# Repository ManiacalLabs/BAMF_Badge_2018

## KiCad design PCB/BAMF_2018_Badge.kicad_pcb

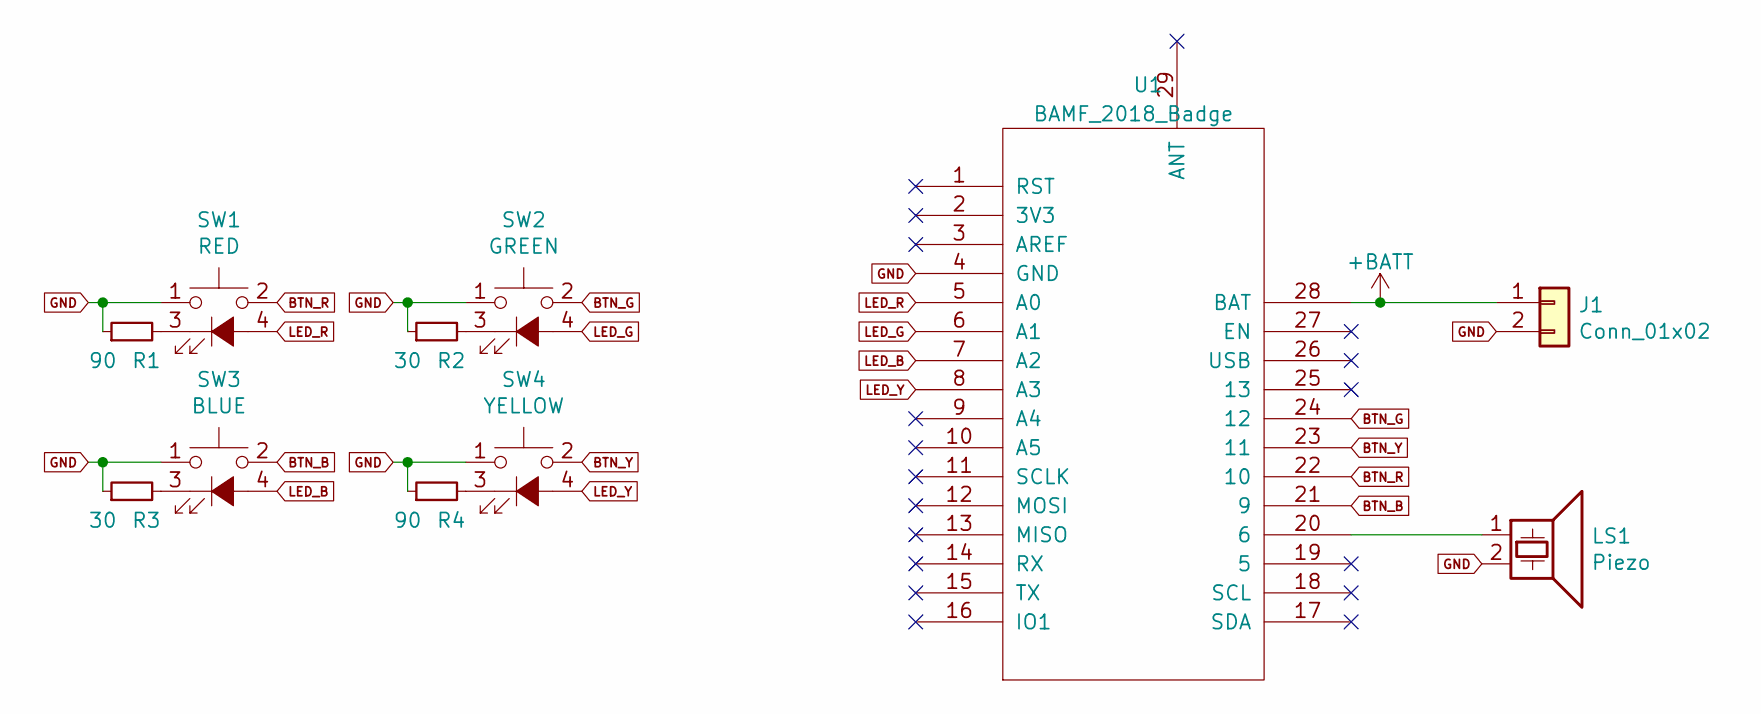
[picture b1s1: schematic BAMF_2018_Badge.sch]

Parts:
J1: Conn_01x02; BATT_CONN
LS1: Piezo; PS1240_Piezo
R1, R4: 90; R_Axial_DIN0204_L3.6mm_D1.6mm_P5.08mm_Horizontal
R2, R3: 30; R_Axial_DIN0204_L3.6mm_D1.6mm_P5.08mm_Horizontal
SW1: RED; SW_PUSH_LED
SW2: GREEN; SW_PUSH_LED
SW3: BLUE; SW_PUSH_LED
SW4: YELLOW; SW_PUSH_LED
U1: BAMF_2018_Badge; FeatherWing_NoOutline_WithAnt

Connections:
+BATT: J1.1, U1.28 (BAT)
BTN_B: SW3.2, U1.21 (9)
BTN_G: SW2.2, U1.24 (12)
BTN_R: SW1.2, U1.22 (10)
BTN_Y: SW4.2, U1.23 (11)
GND: J1.2, LS1.2, R1.1, R2.1, R3.1, R4.1, SW1.1, SW2.1, SW3.1, SW4.1, U1.4 (GND)
LED_B: SW3.4 (A), U1.7 (A2)
LED_G: SW2.4 (A), U1.6 (A1)
LED_R: SW1.4 (A), U1.5 (A0)
LED_Y: SW4.4 (A), U1.8 (A3)
unnamed: LS1.1, U1.20 (6)
unnamed: R1.2, SW1.3 (K)
unnamed: R2.2, SW2.3 (K)
unnamed: R3.2, SW3.3 (K)
unnamed: R4.2, SW4.3 (K)

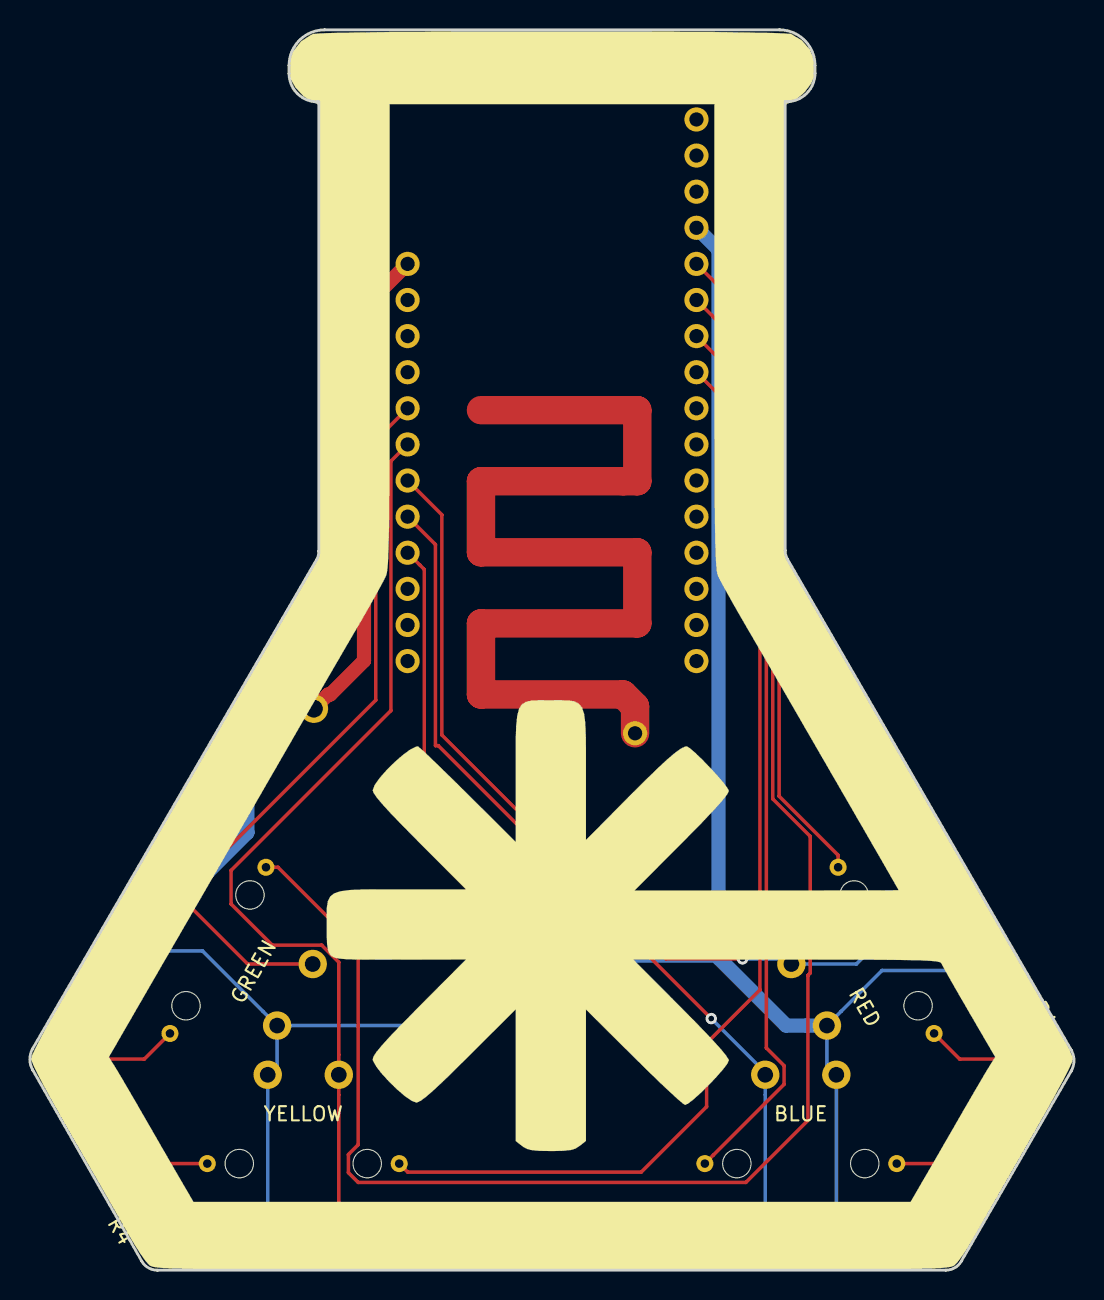
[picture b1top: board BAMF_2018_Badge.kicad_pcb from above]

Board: 2 copper layers, 73.4 x 87.2 mm, 11 parts (1 on the bottom side), 15 nets.

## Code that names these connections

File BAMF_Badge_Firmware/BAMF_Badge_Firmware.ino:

#include "SimonButton.h"
#include "util.h"
#include "rf.h"

// Pins for Adafruit 32u4 RFM69HCW Feather

#define BTN_R 10
#define BTN_G 12
#define BTN_B 9
#define BTN_Y 11

#define LED_R 18 //A0
#define LED_G 19 //A1
#define LED_B 20 //A2
#define LED_Y 21 //A3

#define NOTE_R 523 // C5
#define NOTE_G 659 // E5
#define NOTE_B 784 // G5
#define NOTE_Y 440 // B5

#define NOTE_FAIL 69 //G1
#define NOTE_START 1047 //C6

#define RAND_SEED_PIN 4 //A4

#define SEQ_LEN 32
#define SEQ_STR_LEN SEQ_LEN + 1

#define MODE_DEMO 0
#define MODE_PLAY 1
#define MODE_PLAY_RECV 2

#define SEQ_ON_LEN 500
#define SEQ_BTWN_ON 200

#define PLAY_HOLD_TIME 1200

byte _mode = MODE_DEMO;

char order[] = "RGBY";


//define buttons
SimonButton btns[] = {
  SimonButton(BTN_R, LED_R, NOTE_R, TONE_PIN),
  SimonButton(BTN_G, LED_G, NOTE_G, TONE_PIN),
  SimonButton(BTN_B, LED_B, NOTE_B, TONE_PIN),
  SimonButton(BTN_Y, LED_Y, NOTE_Y, TONE_PIN)
};

char seq_str[SEQ_STR_LEN];
char play_seq_str[SEQ_STR_LEN];
byte seq_pos;
byte play_seq_pos;

void all_off(){
  btns[0].off();
  btns[1].off();
  btns[2].off();
  btns[3].off();
}

void all_on(){
  btns[0].on();
  btns[1].on();
  btns[2].on();
  btns[3].on();
}

bool btn_states[4] = {false, false, false, false};
char btn_state_str[5] = {0,0,0,0,0};
bool check_all(){
  btn_states[0] = btns[0].check();
  btn_states[1] = btns[1].check();
  btn_states[2] = btns[2].check();
  btn_states[3] = btns[3].check();

  btn_state_str[0] = (btn_states[0] ? 'R' : '_');
  btn_state_str[1] = (btn_states[1] ? 'G' : '_');
  btn_state_str[2] = (btn_states[2] ? 'B' : '_');
  btn_state_str[3] = (btn_states[3] ? 'Y' : '_');

  return (btn_states[0] | btn_states[1] | btn_states[2] | btn_states[3]);
}

bool read_all(){
  bool result = false;
  result |= btns[0].read();
  result |= btns[1].read();
  result |= btns[2].read();
  result |= btns[3].read();
  return result;
}

void do_start_play() {
  all_on();
  play_tone_ms(NOTE_START, 500);

  while(read_all()){ delay(5); }

  stop_tone();
  all_off();
  delay(250);

  all_on();
  play_tone(NOTE_START);
  delay(500);
  all_off();
  delay(250);

  all_on();
  play_tone(NOTE_START);
  delay(500);
  all_off();
  delay(250);

  all_on();
  play_tone(NOTE_START);
  delay(500);
  all_off();

  delay(1000);
}

void check_play_hold() {
  read_all();
  if(btns[0].check_hold(PLAY_HOLD_TIME) && btns[1].check_hold(PLAY_HOLD_TIME)) {
    init_play();
    _mode = MODE_PLAY;

    do_start_play();
  }
}

void demo(){
  static byte c = 0;
  all_off();
  delay(SEQ_BTWN_ON);
  // btns[random(0, 4)].on(false);
  btns[c].on(false);
  c++;
  if(c>=4){c = 0;}
  delay(SEQ_ON_LEN);

  check_play_hold();
}

void init_play() {
  memset(seq_str, 0, SEQ_STR_LEN);
  memset(play_seq_str, 0, SEQ_STR_LEN);
  play_seq_pos = seq_pos = 0;

  randomSeed(analogRead(RAND_SEED_PIN));
  for(int i=0; i<SEQ_LEN; i++) {
    seq_str[i] = order[ random(0, 4)];
  }

  send(seq_str, SEQ_LEN); //Send play sequence
  Serial.println("Begin Play!");
}

void play() {
  static byte i;
  static byte b;
  for(i=0; i<=seq_pos; i++) {
    switch(seq_str[i]) {
      case 'R':
        b = 0;
        break;
      case 'G':
        b = 1;
        break;
      case 'B':
        b = 2;
        break;
      case 'Y':
        b = 3;
        break;
      default:
        b = 0;
        break;
    }
    delay(SEQ_BTWN_ON);
    btns[b].on();
    delay(SEQ_ON_LEN);
    btns[b].off();
  }

  static long timeout;
  static int8_t press;
  static bool result;

  // wait for response
  timeout = millis();
  press = -1;
  play_seq_pos = 0;
  result = false;
  while((millis() - timeout) < 5000) {
    if(btns[0].check()) { press = 0; }
    else if(btns[1].check()) { press = 1; }
    else if(btns[2].check()) { press = 2; }
    else if(btns[3].check()) { press = 3; }

    if(press >= 0) {
      timeout = millis(); // reset timeout
      play_seq_str[play_seq_pos] = order[press];

      if(array_cmp(seq_str, play_seq_str, play_seq_pos+1, play_seq_pos+1))
      {
        if(play_seq_pos >= seq_pos) {
          result = true;
          break; //success with full sequence, exit
        }
      }
      else {
        result = false;
        break; // already failed, exit immediately
      }

      play_seq_pos++;
    }
    press = -1;
  }

  if(result){
    seq_pos++;
    if(seq_pos >= SEQ_LEN) {
      Serial.println("WIN!");
      btns[0].on(false);
      btns[1].on(false);
      btns[2].on(false);
      btns[3].on(false);
      delay(500);
      all_off();
      for(i=0; i<4; i++){
        for(b=0; b<4; b++){
          btns[b].on();
          delay(200);
          btns[b].off();
        }
      }
      delay(1000);
      _mode = MODE_DEMO;
      return;
    }
    else {
      delay(500);
    }
  }
  else{
    Serial.println("FAIL");
    for(i=0; i<4; i++){
      play_tone(NOTE_FAIL);
      btns[0].on(false);
      btns[1].on(false);
      btns[2].on(false);
      btns[3].on(false);
      delay(500);
      stop_tone();
      all_off();
      delay(250);
    }
    _mode = MODE_DEMO;
    return;
  }
}

void setup() {
  Serial.begin(115200);
  // while(!Serial){}

  rf_setup();
}

void loop() {
  // check_all();
  // return;

  switch(_mode) {
    case MODE_DEMO:
      demo();
      break;
    case MODE_PLAY:
    case MODE_PLAY_RECV:
      play();
      break;
  }

  char recv_buf[RF_MSG_LEN + 1];
  uint8_t len = RF_MSG_LEN;

  memset(recv_buf, 0, RF_MSG_LEN + 1);

  if(recv(recv_buf, &len)) {
    if(len >= SEQ_LEN){
      Serial.print("RECV: ");
      Serial.println(recv_buf);
      memset(seq_str, 0, SEQ_STR_LEN);
      memcpy(seq_str, recv_buf, SEQ_LEN);
      _mode = MODE_PLAY_RECV;
      play_seq_pos = seq_pos = 0;

      do_start_play();
    }
  }
}

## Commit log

2018-04-06 Mostly working game mode - local only
2018-04-06 Goes into play mode
2018-04-08 Adding PCB
2018-04-10 Reduced bottom layer ground pour (flask half full)
2018-04-11 Adding final silk
2018-04-24 Update for PCB pin ordering
2018-04-27 Pre-wireless update
2018-04-28 adding rf
2018-05-01 Working broadcast
2018-05-02 Reworked sequencing. Ready for MODE_PLAY_RECV
2018-05-06 First working multi-badge support
2018-05-06 small tweaks
